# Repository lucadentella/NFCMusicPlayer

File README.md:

# NFCMusicPlayer

Portable MP3 music player with NFC tags control

## Features :trophy:

 - **SD card** reader
 - **Battery** powered with built-in **USB-C charger**
 - **Web based** configuration (map NFC tags to songs)
 - **Arduino** based firmware
 - **3D printed** enclosure

## :movie_camera: Tutorial
- [Youtube video - English](https://youtu.be/ck0IdwVWIIs)
- [Youtube video - Italiano](https://youtu.be/Wxny4k97sL8)

## :notebook: Documentation
 - [Part list](https://github.com/lucadentella/NFCMusicPlayer/tree/main/documentation/partlist.md)
 - [Some tips for building it](https://github.com/lucadentella/NFCMusicPlayer/tree/main/documentation/tips.md)
 - [Troubleshooting - Error codes](https://github.com/lucadentella/NFCMusicPlayer/tree/main/documentation/error-codes.md)

## :wrench: Board
- [Schematics, PDF](https://github.com/lucadentella/NFCMusicPlayer/raw/main/board/NFCMusicPlayer_12-sch.pdf)
- [KiCAD 8 files](https://github.com/lucadentella/NFCMusicPlayer/raw/main/board/)
- [SDcard content](https://github.com/lucadentella/NFCMusicPlayer/raw/main/sdcard/)
- [Project page for ready-made PCBs](https://www.pcbway.com/project/shareproject/NFCMusicPlayer_7cb0c6f8.html)
 
## :gift: Enclosure
- ["Thing" on Thingiverse](https://www.thingiverse.com/thing:6994529)

 ## :floppy_disk: Firmware
 - [Arduino sketch](https://github.com/lucadentella/NFCMusicPlayer/tree/main/firmware/NFCMusicPlayer)
 
**Required libraries**
- [ESP32-audioI2S](https://github.com/schreibfaul1/ESP32-audioI2S) 2.0.0
- [Adafruit_PN532](https://github.com/adafruit/Adafruit-PN532) 1.3.4
- [Async TCP](https://github.com/ESP32Async/AsyncTCP) 3.4.0
- [ESP Async WebServer](https://github.com/ESP32Async/ESPAsyncWebServer) 3.7.7
- [ArduinoJson](https://arduinojson.org/?utm_source=meta&utm_medium=library.properties) 7.4.1
- [Arduino List](https://github.com/nkaaf/Arduino-List) 3.0.1

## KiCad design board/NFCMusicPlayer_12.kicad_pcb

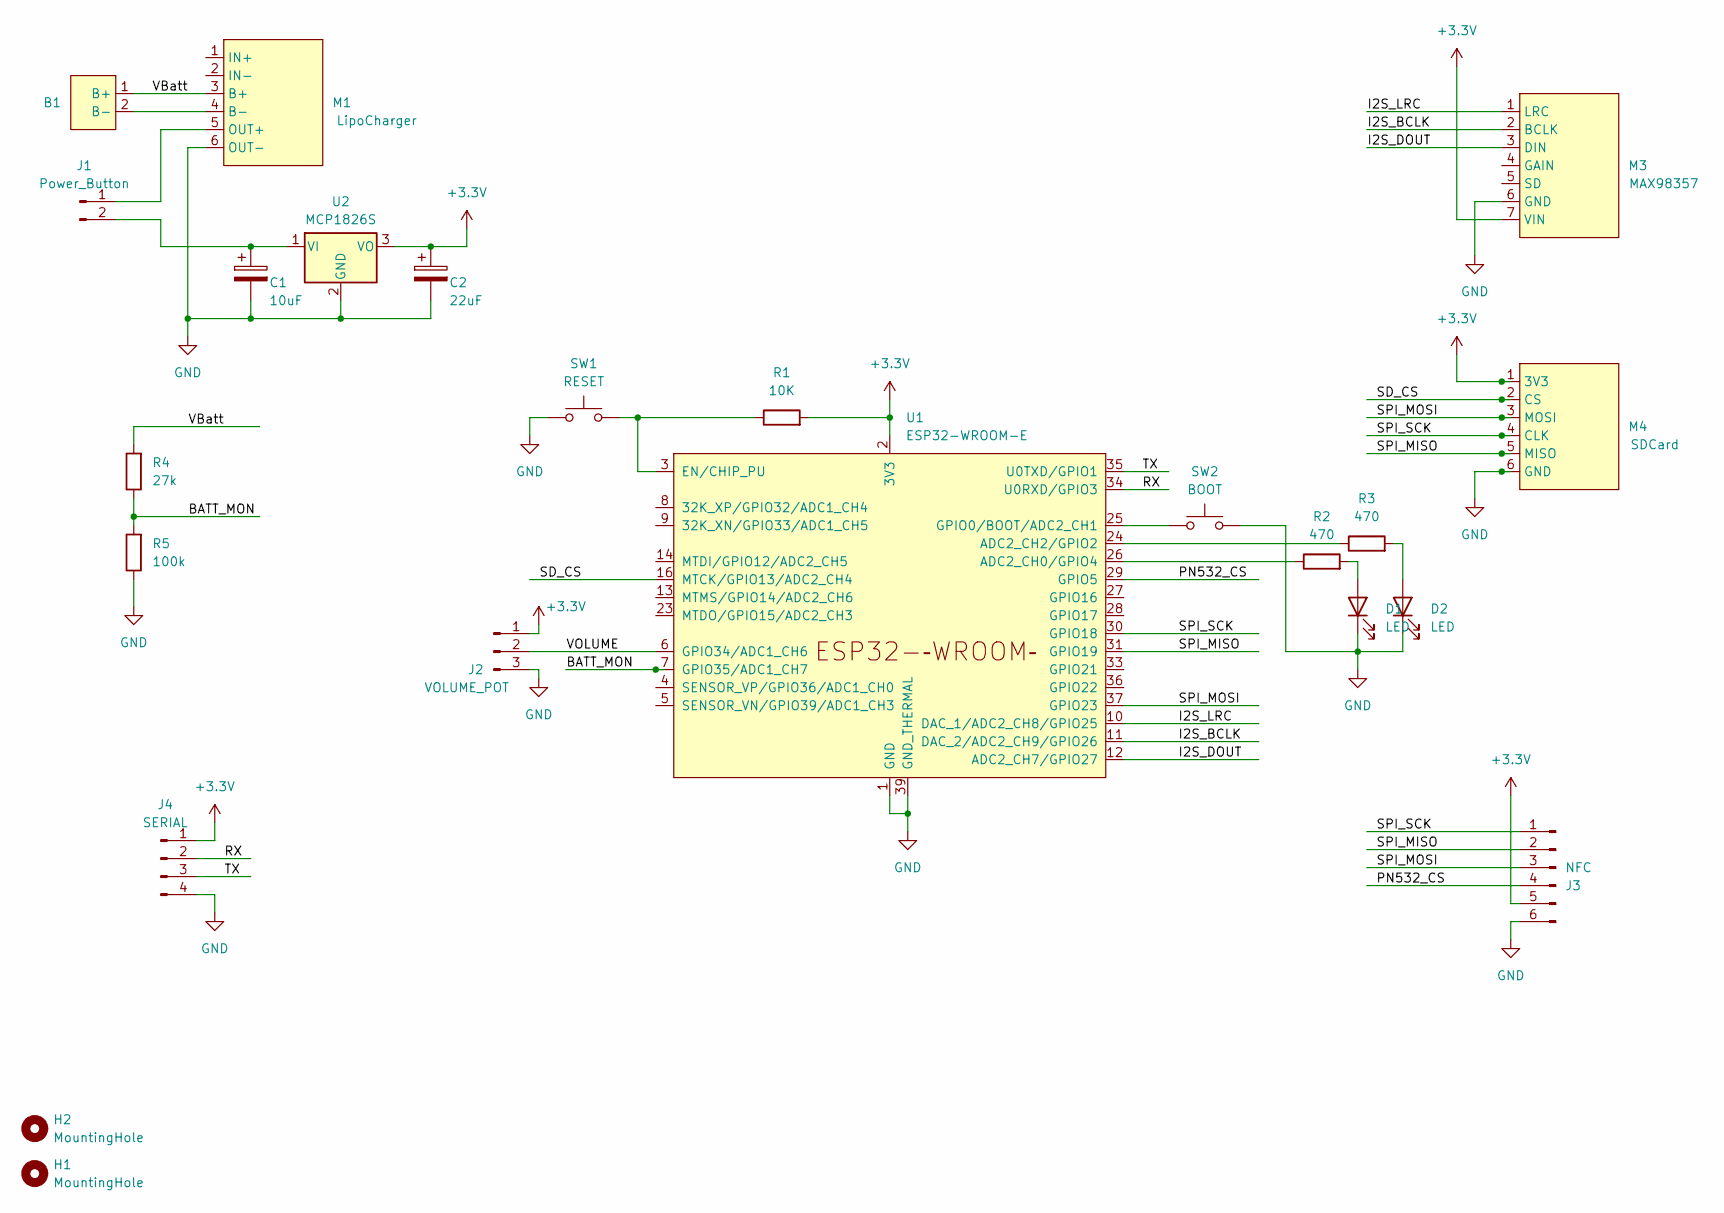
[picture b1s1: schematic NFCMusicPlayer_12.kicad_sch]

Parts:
B1: Battery_Holder
C1: 10uF; CP_Radial_D6.3mm_P2.50mm
C2: 22uF; CP_Radial_D6.3mm_P2.50mm
D1, D2: LED; LED_D5.0mm_Horizontal_O1.27mm_Z9.0mm
H1, H2: MountingHole; MountingHole_3.2mm_M3
J1: Power_Button; PinHeader_1x02_P2.54mm_Vertical
J2: VOLUME_POT; PinHeader_1x03_P2.54mm_Vertical
J3: NFC; PinHeader_1x06_P2.54mm_Vertical
J4: SERIAL; PinHeader_1x04_P2.54mm_Vertical
M1: LipoCharger; LipoCharger_Module
M3: MAX98357; MAX98357_Module
M4: SDCard; MicroSD_Module
R1: 10K; R_Axial_DIN0207_L6.3mm_D2.5mm_P2.54mm_Vertical
R2, R3: 470; R_Axial_DIN0207_L6.3mm_D2.5mm_P2.54mm_Vertical
R4: 27k; R_Axial_DIN0207_L6.3mm_D2.5mm_P2.54mm_Vertical
R5: 100k; R_Axial_DIN0207_L6.3mm_D2.5mm_P2.54mm_Vertical
SW1: RESET; SW_PUSH_6mm_H5mm
SW2: BOOT; SW_PUSH_6mm_H5mm
U1: ESP32-WROOM-E; ESP32-WROOM-32E
U2: MCP1826S; TO-220-3_Vertical

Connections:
+3.3V: C2.1, J2.1, J3.5, J4.1, M3.7 (VIN), M4.1 (3V3), R1.2, U1.2 (3V3), U2.3 (VO)
/BATT_MON: R4.1, R5.2, U1.7 (GPIO35/ADC1_CH7)
/I2S_BCLK: M3.2 (BCLK), U1.11 (DAC_2/ADC2_CH9/GPIO26)
/I2S_DOUT: M3.3 (DIN), U1.12 (ADC2_CH7/GPIO27)
/I2S_LRC: M3.1 (LRC), U1.10 (DAC_1/ADC2_CH8/GPIO25)
/PN532_CS: J3.4, U1.29 (GPIO5)
/RX: J4.2, U1.34 (U0RXD/GPIO3)
/SD_CS: M4.2 (CS), U1.16 (MTCK/GPIO13/ADC2_CH4)
/SPI_MISO: J3.2, M4.5 (MISO), U1.31 (GPIO19)
/SPI_MOSI: J3.3, M4.3 (MOSI), U1.37 (GPIO23)
/SPI_SCK: J3.1, M4.4 (CLK), U1.30 (GPIO18)
/TX: J4.3, U1.35 (U0TXD/GPIO1)
/VBatt: B1.1 (B+), M1.3 (B+), R4.2
/VOLUME: J2.2, U1.6 (GPIO34/ADC1_CH6)
GND: C1.2, C2.2, D1.1 (K), D2.1 (K), J2.3, J3.6, J4.4, M1.6 (OUT-), M3.6 (GND), M4.6 (GND), R5.1, SW1.1, SW2.2, U1.1 (GND), U1.15 (GND), U1.38 (GND), U1.39 (GND_THERMAL), U2.2 (GND)
unnamed: B1.2 (B-), M1.4 (B-)
unnamed: D1.2 (A), R2.2
unnamed: D2.2 (A), R3.2
unnamed: J1.1, M1.5 (OUT+)
unnamed: C1.1, J1.2, U2.1 (VI)
unnamed: R2.1, U1.26 (ADC2_CH0/GPIO4)
unnamed: R3.1, U1.24 (ADC2_CH2/GPIO2)
unnamed: R1.1, SW1.2, U1.3 (EN/CHIP_PU)
unnamed: SW2.1, U1.25 (GPIO0/BOOT/ADC2_CH1)

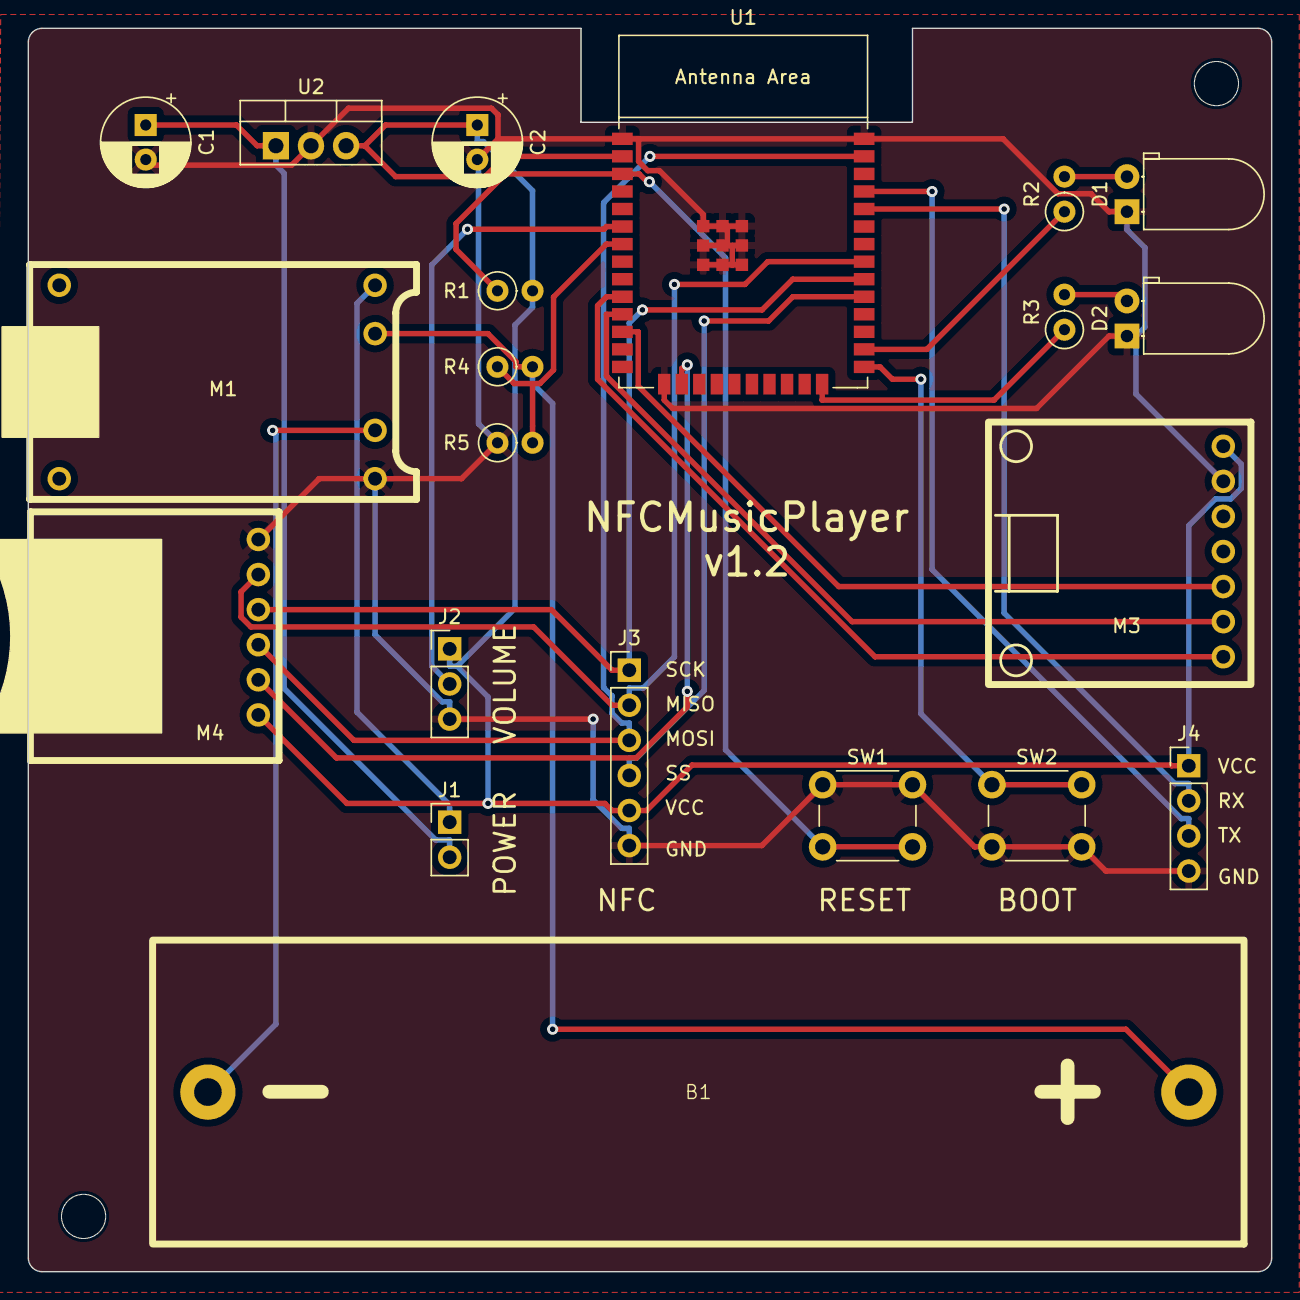
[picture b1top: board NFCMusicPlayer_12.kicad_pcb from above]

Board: 2 copper layers, 90.0 x 90.0 mm, 23 parts (0 on the bottom side), 24 nets.

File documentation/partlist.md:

# :wrench: Part list

| ID | Description | Link | 
|--|--|--|
| R1 | Resistor, 10Kohm 1/4W | (n/a)
| R2, R3 | Resistor, 470ohm 1/4W | (n/a)
| R4 | Resistor, 27Kohm 1/4W | (n/a)
| R5 | Resistor, 100Kohm 1/4W | (n/a)
| R1 | Resistor, 470ohm 1/4W | (n/a)
| C1 | Capacitor, Electrolytic 10uF 25V | (n/a)
| C2 | Capacitor, Electrolytic 22uF 25V | (n/a)
| D1, D2 | 5mm LED | (n/a)
| RESET, BOOT | PCB switch | (n/a)
| U1 | ESP32 WROOM-32E Module (4Mb) | [https://www.aliexpress.com/item/1005002032158386.html](https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
| U2 | MCP1826S Voltage Regulator | (n/a)
||||
| M1 | 3.7V TP4056 Lithium Battery Charger Protect Type-C Board | [https://www.aliexpress.com/item/1445006612.html](https://www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
| M3 | MAX98357A I2S 3W Class D Amplifier Breakout board | [https://www.aliexpress.com/item/1005006209483760.html](https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
| M4 | Mini SD Module | [https://www.aliexpress.com/item/1005001861949506.html](https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
| NFC | PN532 NFC RFID Wireless Module V3 | [https://www.aliexpress.com/item/1005001792108376.html](https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
||||
| B1 | ABS 18650 1X Battery Holder | [https://www.aliexpress.com/item/1005001991113047.html](https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
| BUTTON | SPST 16.3mm 2 Pin Round Switch  | [https://www.aliexpress.com/item/1005002032158386.html](https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
| POT | RK097N 10Kohm potentiometer  | [https://www.aliexpress.com/item/1005001417073667.html](https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
| SPEAKER | AIYIMA 2 Inch 4 Ohm 3W Full Range Speaker | [https://www.aliexpress.com/item/32593991938.html](https://ww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
||||
| CASE | 3D Printed Case | [https://www.thingiverse.com/](https://www.thingiverse.com/)
| INSERTS | M3 5x5mm Brass Inserts  | [https://www.aliexpress.com/item/1005003582355741.html](https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
| SCREWS | M3 8mm, 10mm, 12mm | (n/a)

NOTE: Links are provided for reference only: most of the items are available on different stores

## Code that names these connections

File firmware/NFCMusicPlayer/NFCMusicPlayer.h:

// Required libraries
#include <Audio.h>
#include <FS.h>
#include <SD.h>
#include <SPI.h>
#include <Adafruit_PN532.h>
#include <WiFi.h>
#include <AsyncTCP.h>
#include <ESPAsyncWebSrv.h>
#include <ArduinoJson.h>
#include <AsyncJson.h>
#include <List.hpp>

// to disable brownout
#include "soc/soc.h"
#include "soc/rtc_cntl_reg.h"

// PINs
#define SD_CS         13
#define PN532_CS      5
#define SPI_MOSI      23//15
#define SPI_MISO      19//2
#define SPI_SCK       18//14
#define I2S_DOUT      27//16
#define I2S_BCLK      26
#define I2S_LRC       25
#define PLAY_LED      2
#define STATUS_LED    4
#define VOLUME_PIN    34
#define BATTERY_PIN   35

// Configuration
#define NFC_READ_INTERVAL   2000
#define VOLUME_SAMPLES      200
#define MAX_SLOTS           20
#define MAPPINGS_FILE       "/mappings.txt"
#define MUSIC_FOLDER        "/music"
#define WEBUI_FOLDER        "/web/"
#define AP_SSID             "NFCMusicPlayer"
#define AP_PASSWORD         "MyMusicPlayer"


// Struct and array for mapping between tags and songs
typedef struct {
  String tagid;
  String song;
} mapping;
List<mapping> mappings;

// Global objects
SPIClass spi = SPIClass(VSPI);
Adafruit_PN532 nfc(PN532_CS, &spi);
Audio audio;
AsyncWebServer server(80);

// Global variables
TaskHandle_t nfcTaskHandler;
String tagID;
bool nfcPresent = false;
bool playing = false;
long lastReadTime = -1;
long volumeSamplesSum = 0;
int volumeSamples = 0;
int currentVolume = 10;

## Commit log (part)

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2025-03-29 Project updated
2025-03-29 Thingiverse link updated
2025-03-29 SD card content
2025-03-29 Firmware added
2025-04-01 Add tips page (closes #1 )
2025-04-01 Homepage updated
2025-05-25 List of required libraries added (closes #2)
2025-05-25 Fix typo

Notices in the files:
README.md:
License: CC-BY-NC-SA
